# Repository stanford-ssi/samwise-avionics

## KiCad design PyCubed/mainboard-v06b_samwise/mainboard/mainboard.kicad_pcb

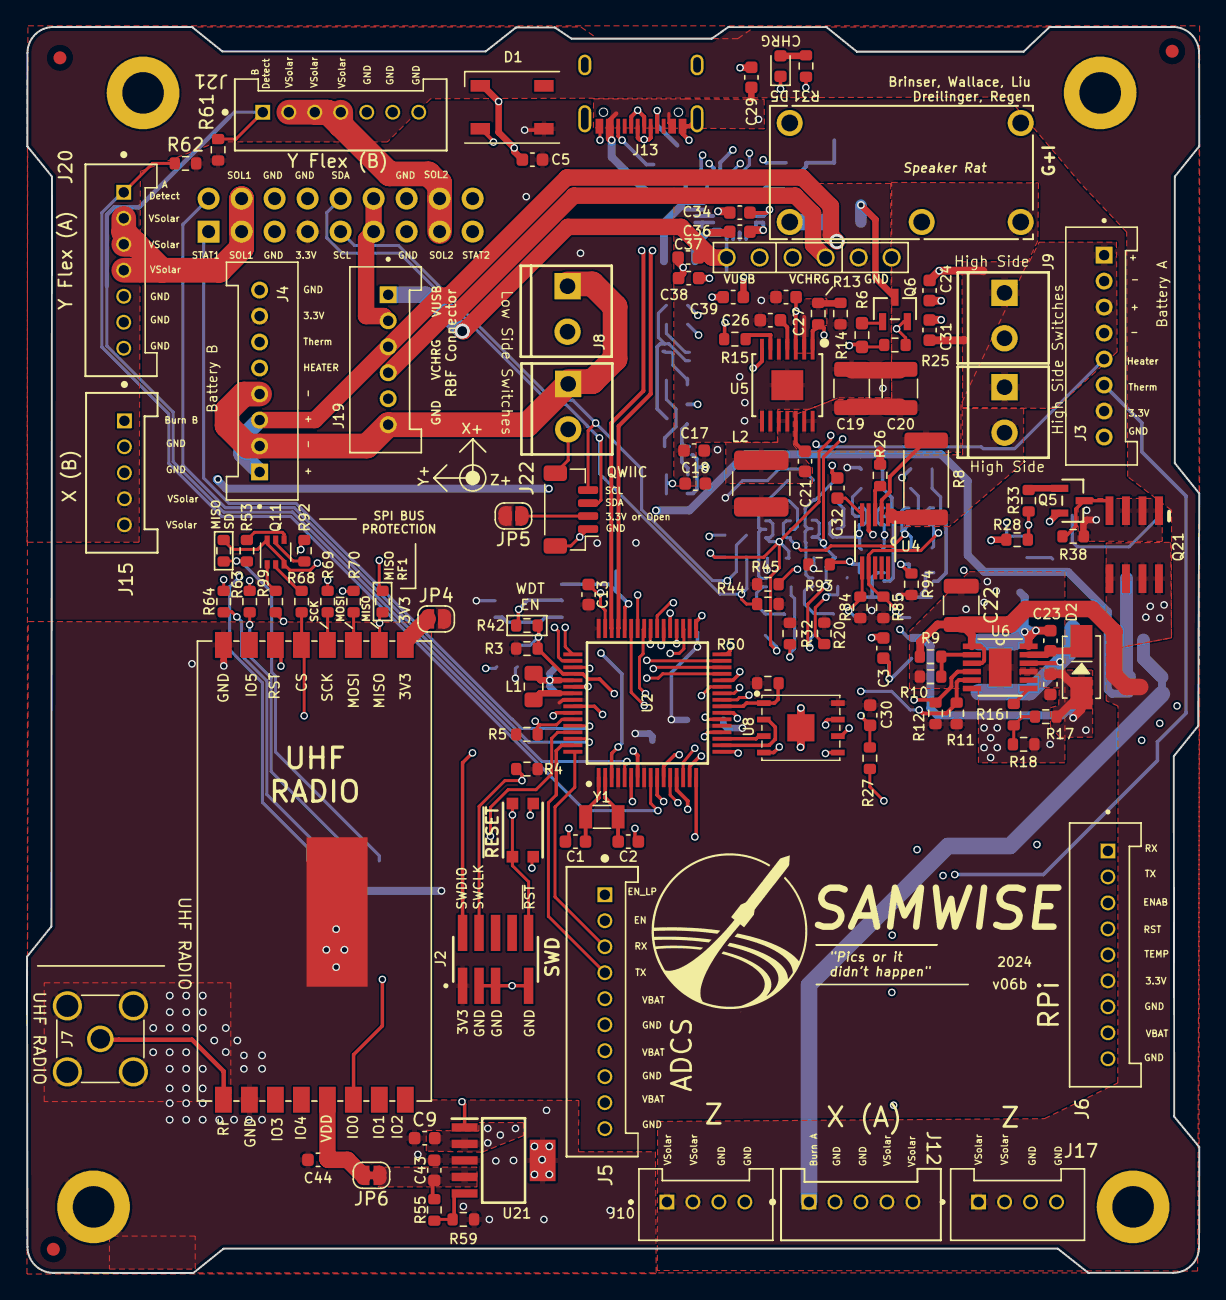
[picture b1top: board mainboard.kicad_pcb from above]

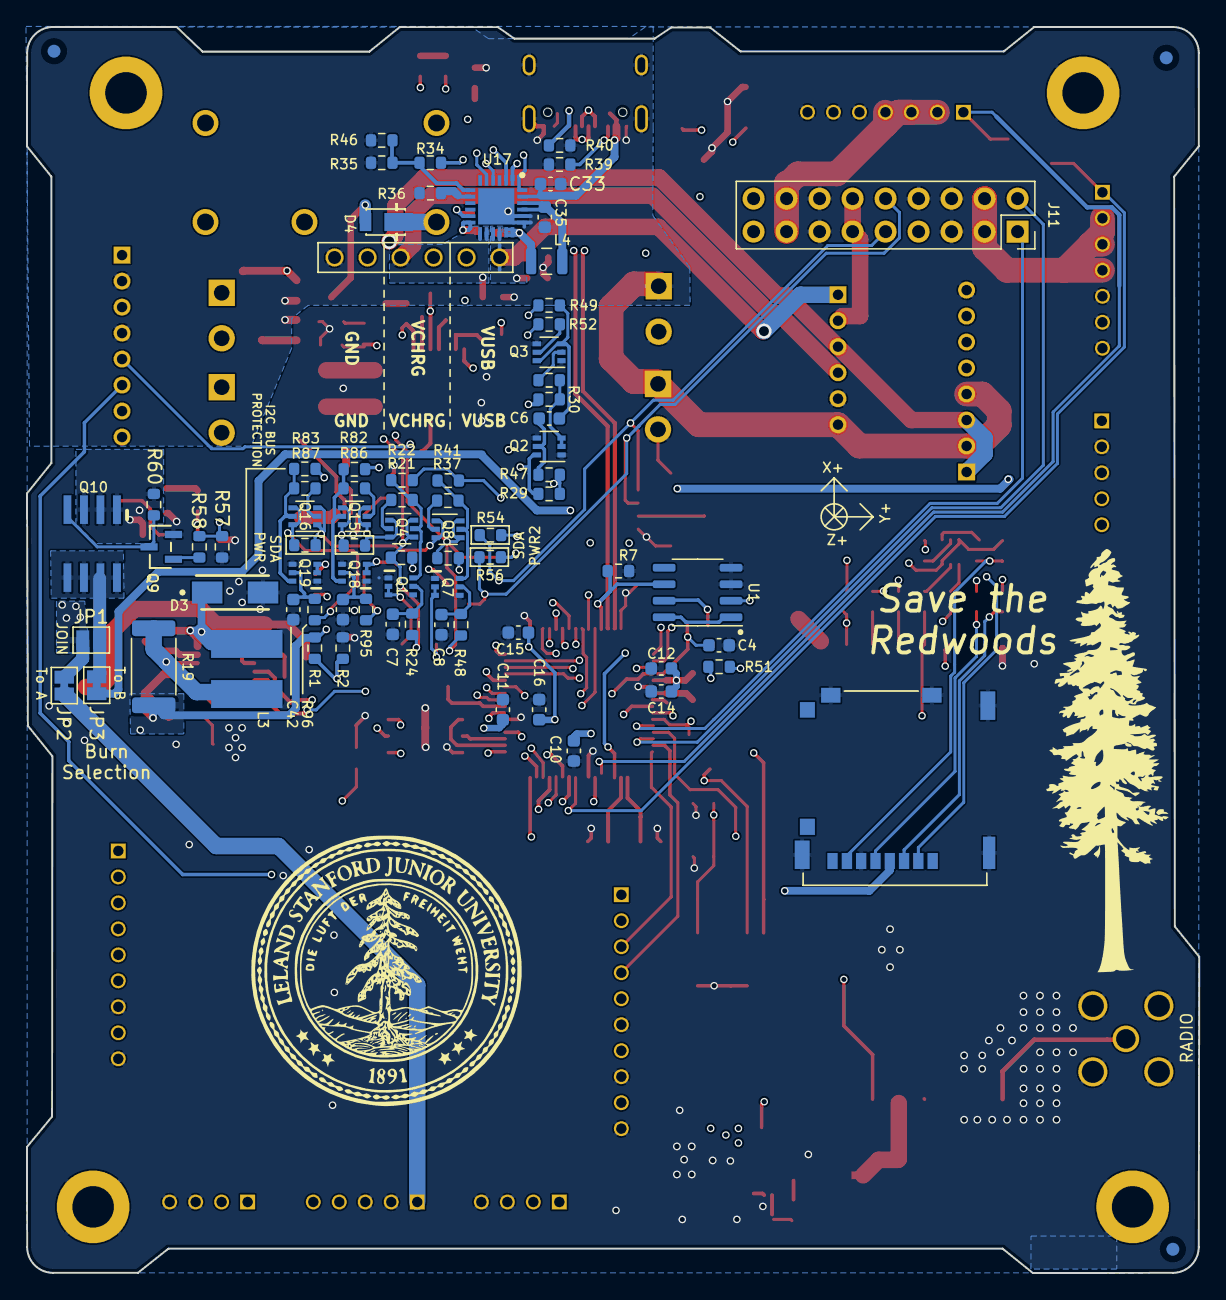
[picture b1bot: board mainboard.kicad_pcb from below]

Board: 4 copper layers, 90.2 x 95.9 mm, 201 parts (79 on the bottom side), 144 nets.

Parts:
C1, C2: 8pF; C_0603_1608Metric
C3, C5, C10, C11, C21, C24, C30: 0.1uF; C_0603_1608Metric
C4, C12, C13, C15, C23, C27, C33: 1uF; C_0603_1608Metric
C6, C9, C14, C16, C25, C35, C39, C43, C44: 10uF; C_0603_1608Metric
C7, C8, C41, C42: 10nF; C_0603_1608Metric
C17, C18, C31, C37, C38: 22uF; C_0603_1608Metric
C19, C20, C22: 10uF; C_1210_3225Metric
C26, C32: 3.3nF; C_0603_1608Metric
C29, C34: 4.7uF; C_0603_1608Metric
C36: 47nF; C_0603_1608Metric
D1: SK6812; LED_WS2812B_PLCC4_5.0x5.0mm_P3.2mm
D2: CDBA240LL; DO-214AC
D3: CMSH1-40M; DIOM5226X262N
D4: DFLS130L; PWRDI-123
D5: GREEN LED; LED_0603_1608Metric
H1, H2, H3, H4: MountingHole_Pad; MountingHole_3.2mm_M3_DIN965_Pad
J1: 503182-1852; MOLEX_503182-1852
J2: Conn_ARM_JTAG_SWD_10; SAMTEC_FTSH-105-01-L-DV-007
J3, J4: 353620850
J5: 353621050; MOLEX_35362-1050
J6: 353620950; MOLEX_35362-0950
J7: Amphenol_901-144; SMA_901-144-horizontal
J8, J9, J16, J18: 1985807; SCREWTERMINAL-3.5MM-2_LOCK
J10, J17: 353620450; MOLEX_35362-0450
J11: MPPT board; PinSocket_2x09_P2.54mm_Vertical
J12, J15: 353620550; MOLEX_35362-0550
J13: USB_C_pycubed; USB_C_Receptacle_XKB_U262-161N-4BVC11
J14: Conn_01x06_Horizontal; PinHeader_1x06_P2.54mm_Vertical_J14
J19: 353620650; MOLEX_35362-0650
J20, J21: 353620750; MOLEX_35362-0750
J22: QWIIC; JST_SH_BM04B-SRSS-TB_1x04-1MP_P1.00mm_Vertical
JP1: Jumper_2_Open; SolderJumper-2_P1.3mm_Open_Pad1.0x1.5mm
JP2, JP3: Jumper_2_Bridged; SolderJumper-2_P1.3mm_Bridged_Pad1.0x1.5mm
JP4: 3.3V EN; SolderJumper-2_P1.3mm_Open_RoundedPad1.0x1.5mm
JP5: QWIIC suply; SolderJumper-2_P1.3mm_Open_RoundedPad1.0x1.5mm
JP6: Jumper_3_Bridged12; SolderJumper-2_P1.3mm_Bridged_RoundedPad1.0x1.5mm
L1: 10uH; L_0805_2012Metric_Pad1.15x1.40mm_HandSolder
L2: 3.3uH; L_2141
L3: 68uH; SDE06004A-680K
L4: 1uH; L_2510
Q1, Q7, Q18, Q19: BSS138DWQ-7
Q2, Q3, Q4, Q8, Q15, Q16: MBT2222ADW1T1; SOT-363_SC-70-6
Q5, Q9: IRLML2803; SOT-23
Q6: BC817-40,215; SOT-23
Q10, Q21: DMP2040USS-13; IRF7404TRPBF
Q11: MMDT2907; SOT-363_SC-70-6
R1, R18: 330k; R_0603_1608Metric
R2: 110k; R_0603_1608Metric
R3, R4, R5, R7, R22, R23, R25, R28, R31, R41, R43, R44, R45, R46, R50, R51, R52, R55, R57, R82, R83, R84, R85: 10k; R_0603_1608Metric
R6: 2.1k; R_0603_1608Metric_Pad0.98x0.95mm_HandSolder
R8: 0.02; R_2512_6332Metric
R9: 121k; R_0603_1608Metric
R10, R14: 22.1k; R_0603_1608Metric
R11, R12, R15, R20, R27, R30, R32, R38, R49, R60, R61, R62, R93, R94: 100k; R_0603_1608Metric
R13, R29: 73.2k; R_0603_1608Metric
R16: 50k; R_0603_1608Metric
R17: 510k; R_0603_1608Metric
R19: 0.40; R_2512_6332Metric
R21, R37, R86, R87: 680; R_0603_1608Metric
R24, R47, R48, R95, R96: 200k; R_0603_1608Metric
R26, R63, R64, R69, R70: 1k; R_0603_1608Metric
R33, R58, R68, R92: 4.7k; R_0603_1608Metric
R34: 5.23k; R_0603_1608Metric
R35: 30.1k; R_0603_1608Metric
R36: 560; R_0603_1608Metric
R39, R40: 5.1k; R_0603_1608Metric
R42: 100; R_0603_1608Metric
R53, R54, R56, R99, R101, R104, R108, R109: 0; R_0603_1608Metric
R59: 3.3k; R_0603_1608Metric
R110: 20k; R_0603_1608Metric
REF1B, REF1T, REF2B, REF2T, REF3B, REF3T: Fiducial_1mm_Mask2mm
SW1: KMR231NG LFS; BTN_KMR2_4.6X2.8
U1: MAX706RESA; SO-8_3.9x4.9mm_P1.27mm
U2: ATSAMD51J20A-AU; QFP50P1200X1200X120-64N
U4: ADM1176-1ARMZ-R7
U5: TPS54226PWPR; PWP14_2P31X2P46-L
U6: LT3652HVIMSE#PBF; MSOP-12_MSE
U8: MR25H40MDF; SON127P600X500X90-9N
U16: PE014006; RELAY_PE014006
U17: BQ25883RGER; QFN50P400X400X100-25N-D
U21: TPS7A4501DCQT
U23: RFM98PW
Y1: 32.768kHz; Crystal_SMD_3215-2Pin_3.2x1.5mm

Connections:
3.3V: C5.1, C10.1, C11.1, C13.1, C15.1, C16.1, C17.2, C18.2, C30.1, D1.1 (VDD), J1.4 (VDD), J2.1 (VTref), J3.7, J4.7, J6.6, J11.7, JP4.2 (B), JP5.2 (B), L2.2, R3.1, R4.1, R5.1, R11.2, R12.2, R13.2, R20.1, R22.1, R23.1, R32.1, R41.1, R43.1, R44.1, R45.1, R50.2, R51.2, R61.1, R62.1, R82.1, R83.1, R84.1, R85.1, R93.1, R94.1, U1.2 (VCC), U2.4 (PA03), U2.8 (VDDANA), U2.21 (VDDIO), U2.34 (VDDIO1), U2.48 (VDDIO2), U2.56 (VDDIO3), U5.1 (VO), U8.8 (VDD)
/Avionics/BATTERY: C3.1, R1.2, R2.2, U2.15 (PA06)
/Avionics/XTAL1: C1.1, U2.1 (PA00), Y1.1
/Avionics/XTAL2: C2.1, U2.2 (PA01), Y1.2
/Burn Wires/BURN_AOUT: JP1.1 (A), JP2.1 (A), Q21.5 (Drain), Q21.6 (Drain), Q21.7 (Drain), Q21.8 (Drain)
/Burn Wires/BURN_BOUT: JP1.2 (B), JP3.1 (A), Q10.5 (Drain), Q10.6 (Drain), Q10.7 (Drain), Q10.8 (Drain)
/Burn Wires/VBURN_A_IN: Q10.1 (Source), Q10.2 (Source), Q10.3 (Source), Q21.1 (Source), Q21.2 (Source), Q21.3 (Source), R38.2, R60.2, U16.11
/Connectors/VSOLAR_DEPL1: J11.3, J11.4, J20.2, J20.3, J20.4
/Connectors/VSOLAR_DEPL2: J11.15, J11.16, J21.2, J21.3, J21.4
/Power/3V3_EN: Q2.6 (C1), R29.2, U5.7 (EN)
/Power/REGN: C34.1, R31.2, U17.11 (REGN)
/Power/V_RF: C43.2, JP6.1 (A), R55.1, U21.4 (OUT)
/RF/RF1_ANT: J7.1 (In), U23.1 (ANT)
ADCS_EN: J5.2, U2.43 (PA22)
ADCS_EN_LP: J5.1, U2.41 (PA20)
ADCS_Rx: J5.3, U2.64 (PB03)
ADCS_Tx: J5.4, U2.63 (PB02)
BAT_HEATER_A: J3.5, U2.39 (PB16)
BAT_HEATER_B: J4.5, U2.40 (PB17)
BURN_A: J12.1, JP2.2 (B)
BURN_B: J15.1, JP3.2 (B)
BURN_RELAY_A: R6.1, R25.1, U2.28 (PB15)
ENAB_BURN_A: R28.1, R33.2, U2.32 (PA15)
ENAB_BURN_B: R57.1, R58.2, U2.14 (PA05)
ENAB_RF: U2.6 (PB05), U21.1 (~SHDN)
FLASH_CS: R50.1, U2.24 (PB11), U8.1 (~CS)
FLASH_IO2: U2.19 (PA10), U8.3 (~WP)
FLASH_IO3: U2.20 (PA11), U8.7 (~HOLD)
FLASH_MISO: U2.18 (PA09), U8.2 (SO)
FLASH_MOSI: U2.17 (PA08), U8.5 (SI)
FLASH_SCK: U2.23 (PB10), U8.6 (SCK)
GND: C1.2, C2.2, C3.2, C4.1, C5.2, C7.2, C8.2, C9.1, C10.2, C11.2, C12.1, C13.2, C14.2, C15.2, C16.2, C17.1, C18.1, C19.2, C20.2, C22.1, C25.1, C26.2, C27.2, C30.2, C32.1, C41.2, C42.2, C43.1, C44.1, D1.3 (VSS), D3.2 (A), H1.1, H2.1, H3.1, H4.1, J1.6 (VSS), J1.P1 (SHIELD), J1.P2 (SHIELD), J1.P3 (SHIELD), J1.P4 (SHIELD), J1.P5 (SHIELD), J2.3 (GND), J2.5 (GND), J2.9 (GNDDetect), J3.8, J4.8, J5.6, J5.8, J5.10, J6.7, J6.9, J7.2 (Ext), J8.2, J10.3, J10.4, J11.5, J11.6, J11.8, J11.13, J11.14, J12.2, J12.3, J14.5, J15.2, J15.3, J17.3, J17.4, J18.2, J19.5, J20.5, J20.6, J20.7, J21.5, J21.6, J21.7, J22.1, J22.MP (MountPin), Q1.1 (S2), Q1.4 (S1), Q2.1 (E1), Q2.4 (E2), Q3.1 (E1), Q3.4 (E2), Q5.2 (S), Q6.2 (E), Q7.1 (S2), Q7.4 (S1), Q9.2 (S), Q18.1 (S2), Q18.4 (S1), Q19.1 (S2), Q19.4 (S1), R2.1, R7.1, R10.2, R14.1, R18.2, R25.2, R27.1, R28.2, R57.2, R59.2, SW1.B (S), SW1.B' (S1), U1.3 (GND), U1.4 (PFI), U2.7 (GND), U2.22 (GND1), U2.33 (GND2), U2.47 (GND3), U2.54 (GND4), U4.4 (GND), U5.5 (GND), U5.8 (PGND1), U5.9 (PGND2), U5.15 (EPAD), U6.6 (TIMER), U6.13 (EPAD), U8.4 (VSS), U8.9 (EP), U16.12, U21.3 (GND_1), U21.6 (GND_2), U23.2 (GND), U23.16 (GND), U23.17 (GND)
GNDREF: C24.2, C29.2, C31.2, C33.1, C34.2, C35.1, C37.1, C38.1, C39.1, J3.2, J3.4, J4.2, J4.4, J8.1, J13.A1 (GND), J13.A12 (GND), J13.S1 (SHIELD), J14.6, J18.1, J19.6, R35.1, R36.1, R39.1, R40.1, R46.1, U17.19 (GND_1), U17.20 (GND_2), U17.25 (EP)
MISO: Q11.3 (C2), Q11.6 (C1), R101.2, R104.2, U2.31 (PA14)
MISO_RF1: R99.2, R101.1, U23.10 (MISO)
MISO_SD: J1.7 (DAT0), R53.2, R104.1
MOSI: R64.2, R70.1, U2.29 (PA12)
MOSI_RF1: R70.2, U23.11 (MOSI)
MOSI_SD: J1.3 (CMD), R64.1
MPPT_STAT_1: J11.1, U2.60 (PB31)
MPPT_STAT_2: J11.17, U2.49 (PB22)
unnamed: D1.4 (DIN), U2.42 (PA21)
unnamed: C23.1, D2.1 (K), U6.11 (BOOST)
unnamed: C23.2, D3.1 (K), L3.1, U6.12 (SW)
unnamed: D5.2 (A), R31.1
unnamed: C37.2, C38.2, J14.1, J19.1, U17.15 (SYS_1), U17.16 (SYS_2)
unnamed: C39.2, J14.4, J19.4, U17.13 (BAT_1), U17.14 (BAT_2)
unnamed: J22.2, JP5.1 (A)
unnamed: JP4.1 (A), U23.9 (3.3V)
unnamed: Q1.6 (D1), Q4.5 (B2), R21.2, R22.2
unnamed: Q1.2 (G2), Q1.3 (D2), R20.2
unnamed: C7.1, Q1.5 (G1), R24.2
unnamed: Q2.2 (B1), Q2.3 (C2), R30.2, R110.2
unnamed: C6.2, Q2.5 (B2), R47.2
unnamed: Q3.2 (B1), R110.1
unnamed: C6.1, Q3.3 (C2), Q3.6 (C1), R49.2
unnamed: Q3.5 (B2), R52.1
unnamed: Q4.2 (B1), R21.1
unnamed: Q5.1 (G), R33.1
unnamed: Q6.1 (B), R6.2
unnamed: D4.A, Q6.3 (C), U16.5 (A2)
unnamed: Q7.6 (D1), Q8.5 (B2), R37.2, R41.2
unnamed: Q7.2 (G2), Q7.3 (D2), R32.2
unnamed: C8.1, Q7.5 (G1), R48.2
unnamed: Q8.2 (B1), R37.1
unnamed: Q9.1 (G), R58.1
unnamed: Q9.3 (D), Q10.4 (Gate), R60.1
unnamed: Q11.2 (B1), R68.1
unnamed: Q11.1 (E1), R99.1
unnamed: Q11.5 (B2), R92.1
unnamed: Q11.4 (E2), R53.1
unnamed: Q15.2 (B1), R86.1
unnamed: Q15.5 (B2), Q18.6 (D1), R82.2, R86.2
unnamed: Q16.2 (B1), R87.1
unnamed: Q16.5 (B2), Q19.6 (D1), R83.2, R87.2
unnamed: Q18.2 (G2), Q18.3 (D2), R93.2
unnamed: C41.1, Q18.5 (G1), R95.2
unnamed: Q19.2 (G2), Q19.3 (D2), R94.2
unnamed: C42.1, Q19.5 (G1), R96.2
unnamed: Q5.3 (D), Q21.4 (Gate), R38.1
unnamed: R16.2, R17.2, R18.1
unnamed: U1.1 (~MR), U1.8 (~WDO)
unnamed: R42.2, U1.7 (~RESET)
unnamed: C12.2, C14.1, L1.1, U2.53 (VDDCORE)
unnamed: L1.2, U2.55 (VSW)
unnamed: R26.2, U4.3 (ON)
unnamed: C32.2, U4.5 (TIMER)
unnamed: R15.1, U5.6 (PG)
unnamed: C26.1, U5.4 (SS)
unnamed: C21.1, L2.1, U5.10 (SW1), U5.11 (SW2)
unnamed: C21.2, U5.12 (VBST)
unnamed: R13.1, R14.2, U5.2 (VFB)
unnamed: C27.1, R15.2, U5.3 (VREG5)
unnamed: L3.2, R19.1, U6.10 (SENSE)
unnamed: R16.1, U6.7 (VFB)
unnamed: R9.2, R10.1, U6.2 (VIN_REG)
unnamed: C36.2, U17.12 (BTST)
unnamed: R36.2, U17.8 (ILIM)
unnamed: C35.2, L4.1, U17.21 (PMID_1), U17.22 (PMID_2)
unnamed: C36.1, L4.2, U17.17 (SW_1), U17.18 (SW_2)
unnamed: R34.2, R35.2, R46.2, U17.7 (TS)
unnamed: R55.2, R59.1, U21.5 (SENSE/ADJ)
RF1_CS: R5.2, R68.2, U2.59 (PB30), U23.13 (NSS)
RF1_IO0: U2.61 (PB00), U23.6 (GPIO_0)
RF1_RST: U2.38 (PA19), U23.14 (RESET)
RPI_ENAB: J6.3, U2.10 (PB07)
RPI_RST: J6.4, R27.2, U2.12 (PB09)
RPI_TEMP: J6.5, U2.13 (PA04)
RPI_UART_FROM_PI: J6.1, U2.36 (PA17)
RPI_UART_TO_PI: J6.2, U2.35 (PA16)
SCK: R63.2, R69.2, U2.30 (PA13)
SCK_RF1: R69.1, U23.12 (SCK)
SCK_SD: J1.5 (CLK), R63.1
SCL: J11.9, J22.4, Q4.1 (E1), Q4.3 (C2), Q15.1 (E1), Q15.3 (C2), R45.2, R54.2, R108.2, U2.26 (PB13)
SCL_PWR: Q15.4 (E2), Q15.6 (C1), R84.2, R95.1, R108.1, U4.6 (SCL)
SCL_PWR2: Q4.4 (E2), Q4.6 (C1), R23.2, R24.1, R54.1, U17.5 (SCL)
SDA: J11.10, J22.3, Q8.1 (E1), Q8.3 (C2), Q16.1 (E1), Q16.3 (C2), R44.2, R56.2, R109.2, U2.25 (PB12)
SDA_PWR: Q16.4 (E2), Q16.6 (C1), R85.2, R96.1, R109.1, U4.7 (SDA)
SDA_PWR2: Q8.4 (E2), Q8.6 (C1), R43.2, R48.1, R56.1, U17.4 (SDA)
SD_CS: J1.2 (CD/DAT3), R51.1, R92.2, U2.51 (PA27)
SENSE_THERM_A: J3.6, U2.16 (PA07)
SENSE_THERM_B: J4.6, U2.3 (PA02)
STAT: D5.1 (K), U17.2 (STAT)
SWCLK: J2.4 (SWDCLK/TCK), R4.2, U2.57 (PA30)
SWDIO: J2.2 (SWDIO/TMS), U2.58 (PA31)
SideDeplyDetectA: J20.1, R62.2, U2.9 (PB06)
SideDeplyDetectB: J21.1, R61.2, U2.5 (PB04)
USB_CC1: J13.A5 (CC1), R40.2
USB_CC2: J13.B5 (CC2), R39.2
USB_D+: J13.A6 (D+), J13.B6 (D+), U2.46 (PA25), U17.24 (D+)
USB_D-: J13.A7 (D-), J13.B7 (D-), U2.45 (PA24), U17.1 (D-)
VBATT: C9.2, C19.1, C20.1, C25.2, D2.2 (A), D4.C, J5.5, J5.7, J5.9, J6.8, J11.11, J11.12, J14.2, J19.2, R1.1, R8.1, R17.1, R19.2, R26.1, R29.1, R30.1, R47.1, R49.1, U4.2 (SENSE), U5.13 (VIN), U5.14 (VCC), U6.9 (BAT), U16.1 (A1), U16.14, U21.2 (IN)
VBATT_SENSE: J9.2, J16.2, R8.2, U4.1 (VCC)
VBUS_IN: C29.1, C33.2, J13.A4 (VBUS), J13.A9 (VBUS), R34.1, U17.23 (VBUS)
VBUS_RESET: R52.2, U2.37 (PA18)
VCC_RF1: C44.2, JP6.2 (B), U23.5 (VCC)
VCHRG: C24.1, C31.1, J3.1, J3.3, J4.1, J4.3, J9.1, J14.3, J16.1, J19.3
VSOLAR: C22.2, J10.1, J10.2, J12.4, J12.5, J15.4, J15.5, J17.1, J17.2, R9.1, U6.1 (VIN), U6.3 (*SHDN)
WDT_WDI: R7.2, U1.6 (~WDI), U2.44 (PA23)
~FIXED_SOLAR_CHRG: R12.1, U2.11 (PB08), U6.4 (*CHRG)
~FIXED_SOLAR_FAULT: R11.1, U2.27 (PB14), U6.5 (*FAULT)
~MPPT_SHDN_1: J11.2, U2.62 (PB01)
~MPPT_SHDN_2: J11.18, U2.50 (PB23)
~RESET: C4.2, J2.10 (~RESET), R3.2, R42.1, SW1.A, SW1.A' (P1), U2.52 (RESETN)

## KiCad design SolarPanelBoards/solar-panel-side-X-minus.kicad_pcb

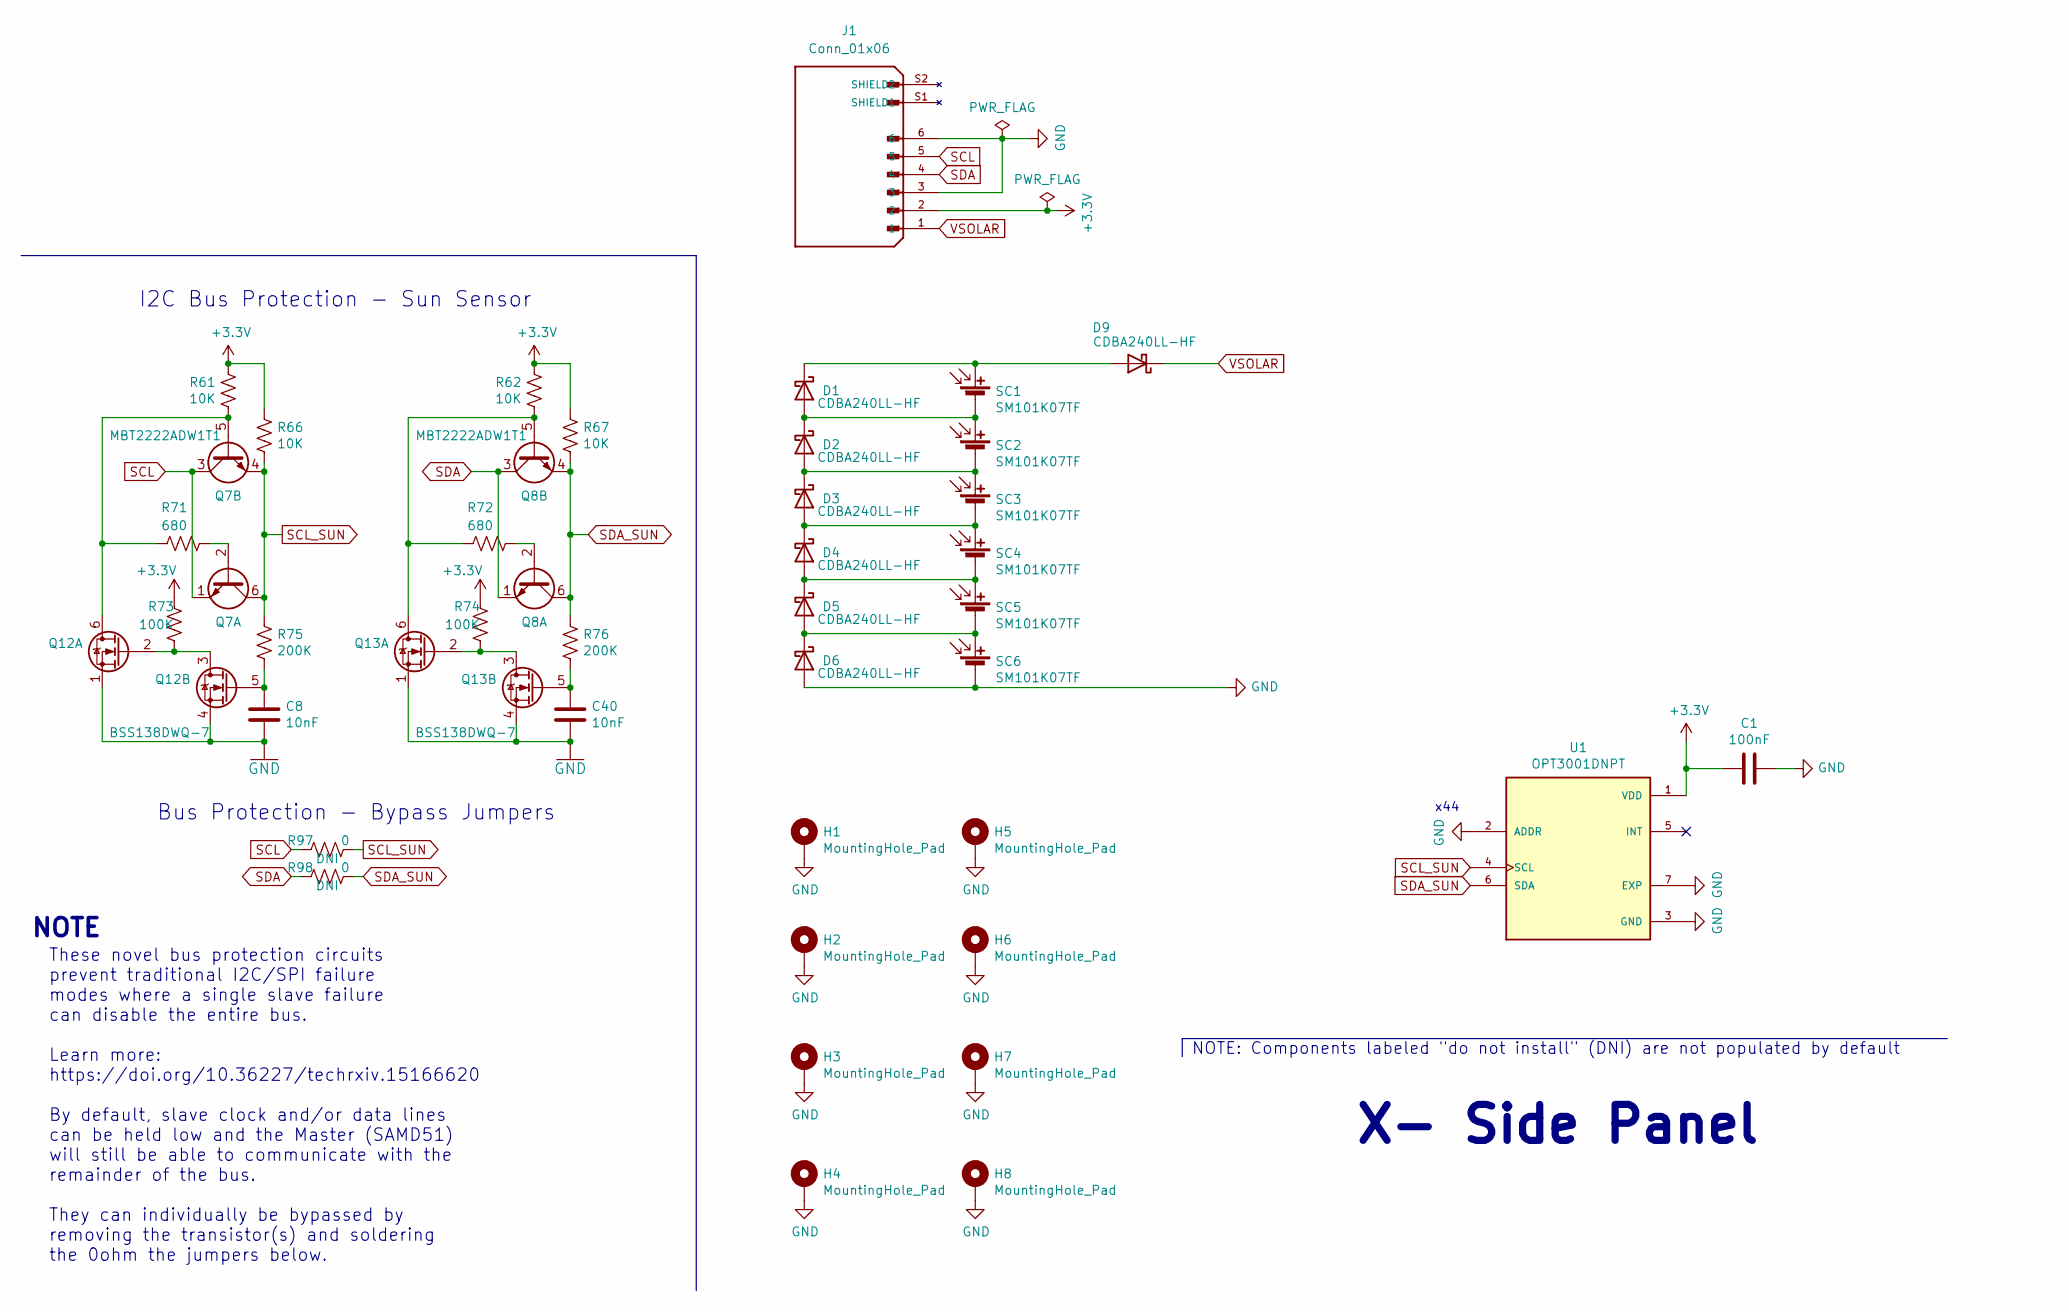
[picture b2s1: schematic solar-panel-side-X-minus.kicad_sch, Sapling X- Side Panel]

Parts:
C1: 100nF; C_0603_1608Metric
C8, C40: 10nF; C_0603_1608Metric
D1, D2, D3, D4, D5, D6, D9: CDBA240LL-HF; DO-214AC
H1, H2, H3, H4, H5, H6, H7, H8: MountingHole_Pad; MountingHole_2.2mm_M2_DIN965_Pad_TopBottom
J1: Conn_01x06; MOLEX_2053380006
Q7, Q8: MBT2222ADW1T1; SOT-363_SC-70-6; Manufacturer_Part_Number MBT2222ADW1T1G
Q12, Q13: BSS138DWQ-7; Manufacturer_Part_Number BSS138DWQ-7; Mouser Part Number 621-BSS138DWQ-7
R61, R62, R66, R67: 10K; R_0603_1608Metric
R71, R72: 680; R_0603_1608Metric
R73, R74: 100K; R_0603_1608Metric
R75, R76: 200K; R_0603_1608Metric
R97, R98: 0; R_0603_1608Metric
SC1, SC2, SC3, SC4, SC5, SC6: SM101K07TF
U1: OPT3001DNPT; OPT3001

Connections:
+3V3: C1.1, J1.2, R61.1, R62.1, R66.1, R67.1, R73.1, R74.1, U1.1 (VDD)
GND: C1.2, C8.2, C40.2, D6.2 (A), H1.1, H2.1, H3.1, H4.1, H5.1, H6.1, H7.1, H8.1, J1.3, J1.6, Q12.1 (S2), Q12.4 (S1), Q13.1 (S2), Q13.4 (S1), SC6.2 (-), U1.2 (ADDR), U1.3 (GND), U1.7 (EXP)
unnamed: D1.2 (A), D2.1 (K), SC1.2 (-), SC2.1 (+)
unnamed: D1.1 (K), D9.2 (A), SC1.1 (+)
unnamed: D2.2 (A), D3.1 (K), SC2.2 (-), SC3.1 (+)
unnamed: D3.2 (A), D4.1 (K), SC3.2 (-), SC4.1 (+)
unnamed: D4.2 (A), D5.1 (K), SC4.2 (-), SC5.1 (+)
unnamed: D5.2 (A), D6.1 (K), SC5.2 (-), SC6.1 (+)
unnamed: Q7.2 (B1), R71.1
unnamed: Q8.2 (B1), R72.1
unnamed: Q7.5 (B2), Q12.6 (D1), R61.2, R71.2
unnamed: Q12.2 (G2), Q12.3 (D2), R73.2
unnamed: C8.1, Q12.5 (G1), R75.2
unnamed: Q8.5 (B2), Q13.6 (D1), R62.2, R72.2
unnamed: Q13.2 (G2), Q13.3 (D2), R74.2
unnamed: C40.1, Q13.5 (G1), R76.2
SCL: J1.5, Q7.1 (E1), Q7.3 (C2), R97.2
SCL_SUN: Q7.4 (E2), Q7.6 (C1), R66.2, R75.1, R97.1, U1.4 (SCL)
SDA: J1.4, Q8.1 (E1), Q8.3 (C2), R98.2
SDA_SUN: Q8.4 (E2), Q8.6 (C1), R67.2, R76.1, R98.1, U1.6 (SDA)
VSOLAR: D9.1 (K), J1.1

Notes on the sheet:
NOTE
x44
I2C Bus Protection - Sun Sensor
X- Side Panel
Bus Protection - Bypass Jumpers
These novel bus protection circuits prevent traditional I2C/SPI failure modes where a single slave failure can disable the entire bus. Learn more: https://doi.org/10.36227/techrxiv.15166620 By default, slave clock and/or data lines can be held low and the Master (SAMD51) will still be able to commu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
NOTE: Components labeled "do not install" (DNI) are not populated by default

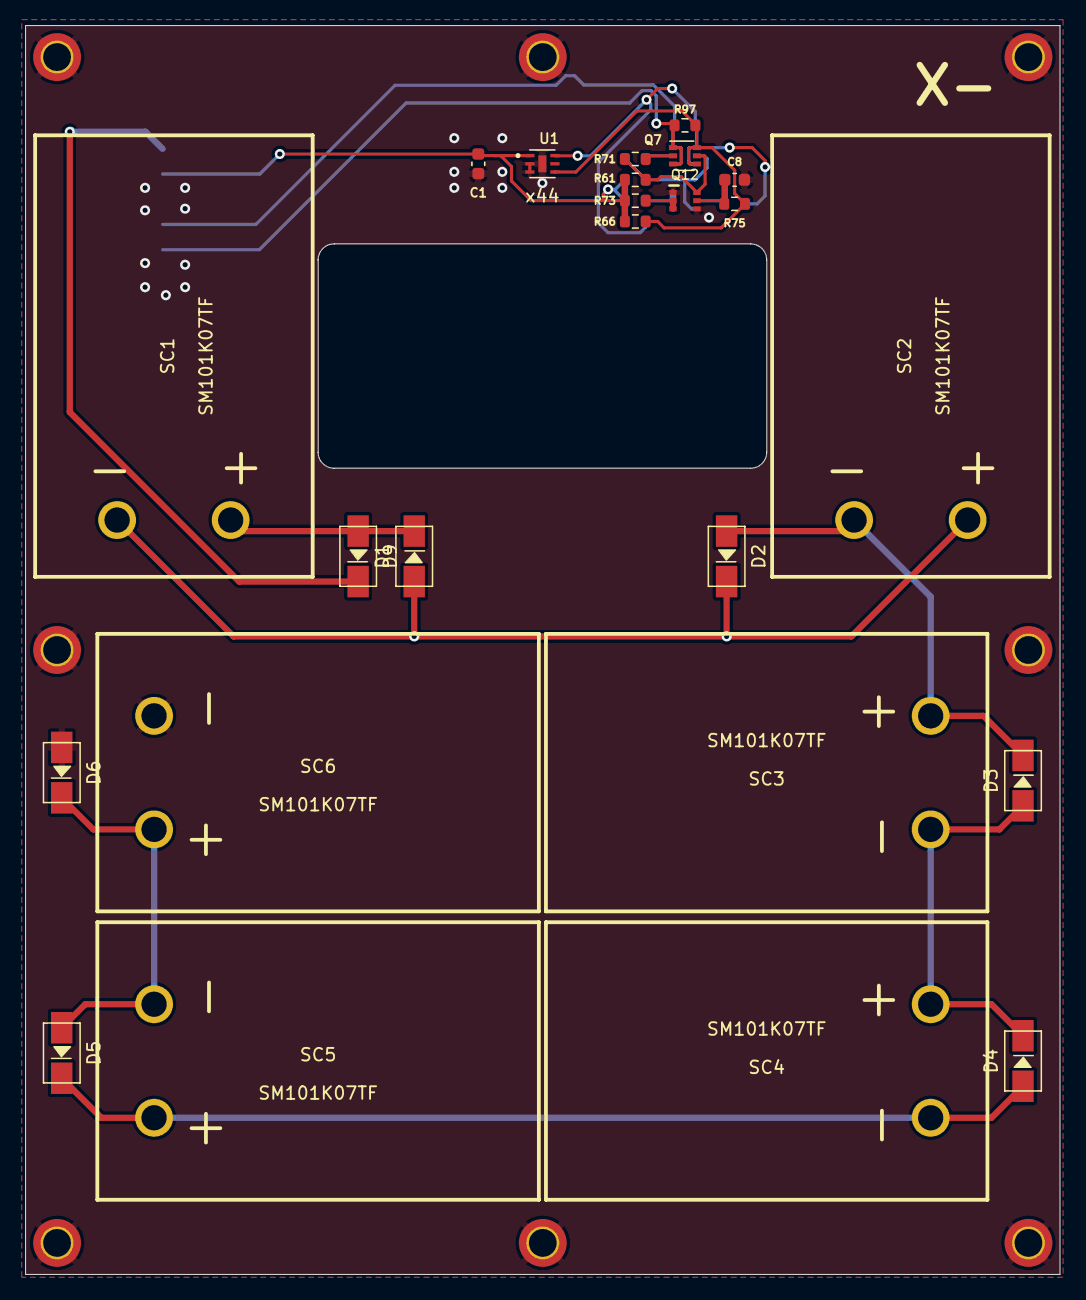
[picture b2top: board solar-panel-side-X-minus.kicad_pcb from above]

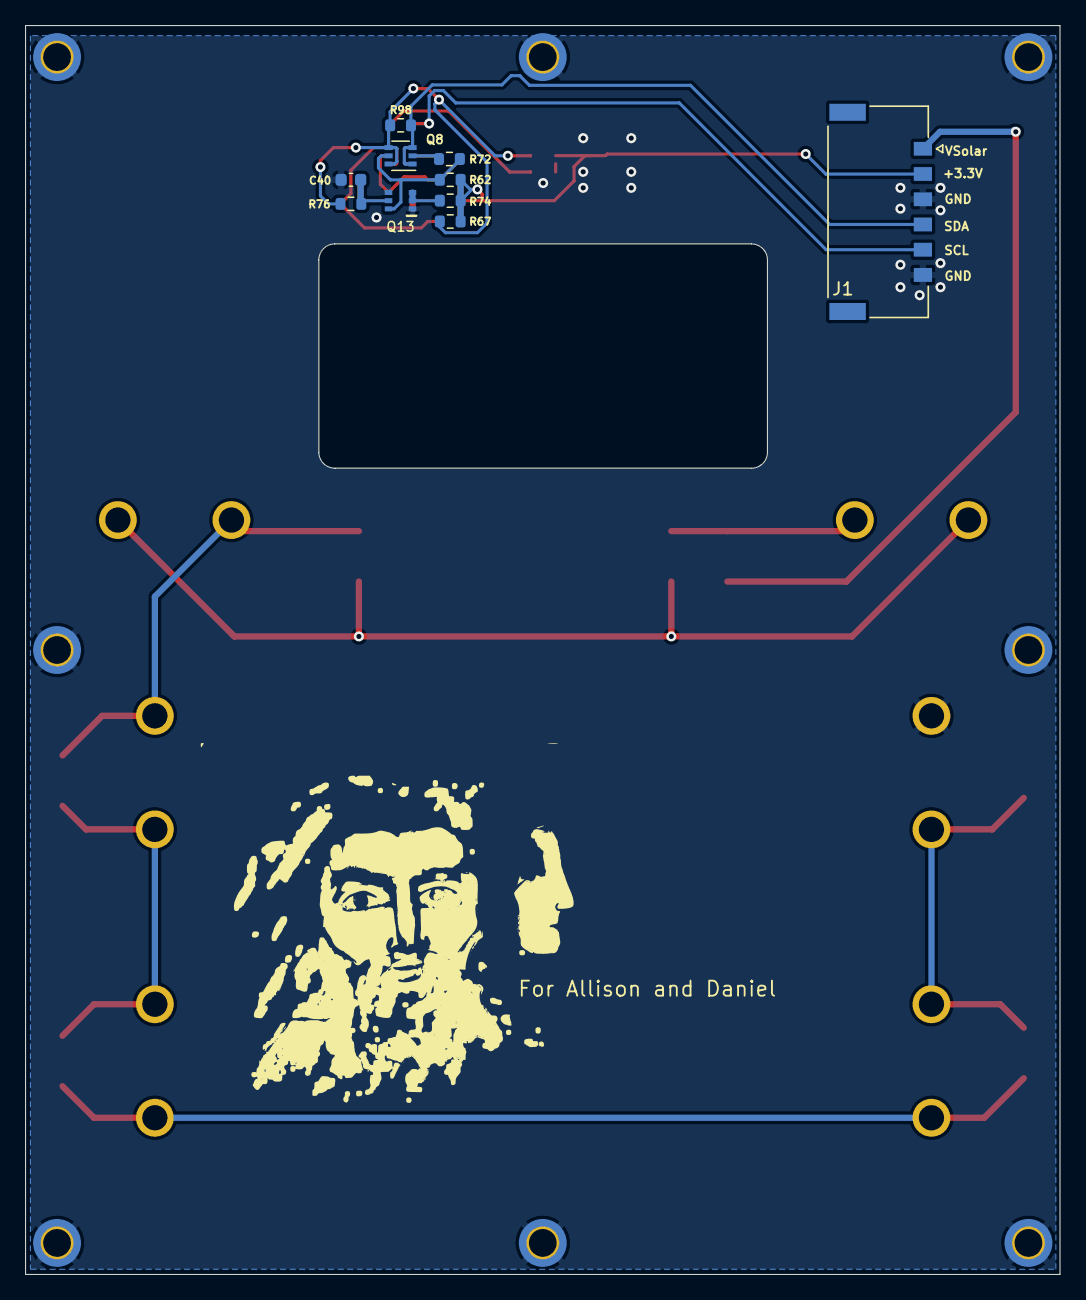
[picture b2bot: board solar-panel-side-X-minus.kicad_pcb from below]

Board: 2 copper layers, 82.0 x 99.0 mm, 42 parts (10 on the bottom side), 21 nets.

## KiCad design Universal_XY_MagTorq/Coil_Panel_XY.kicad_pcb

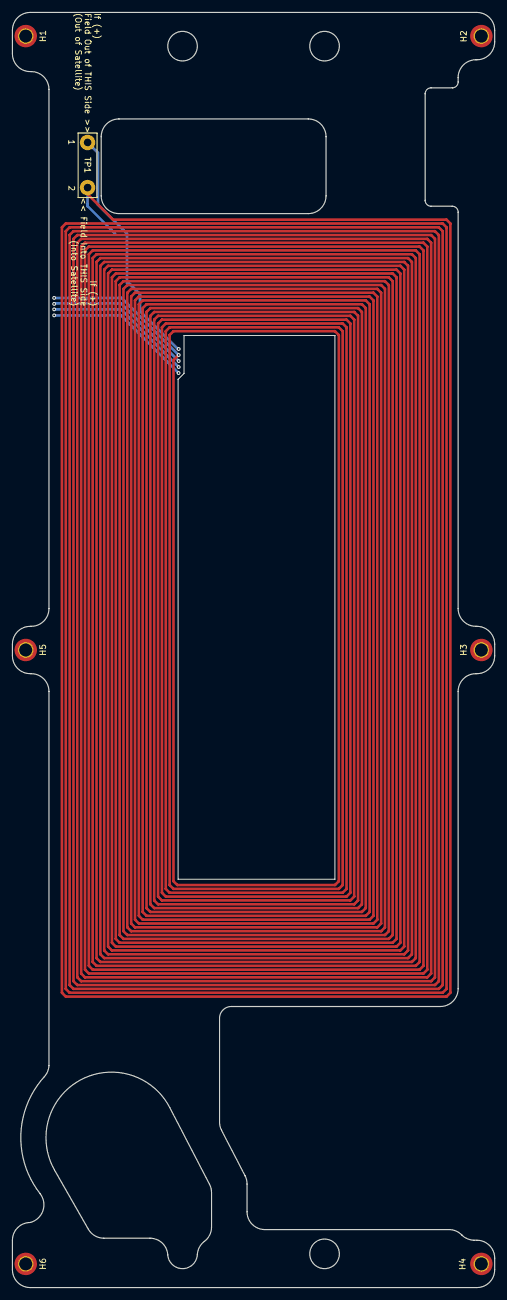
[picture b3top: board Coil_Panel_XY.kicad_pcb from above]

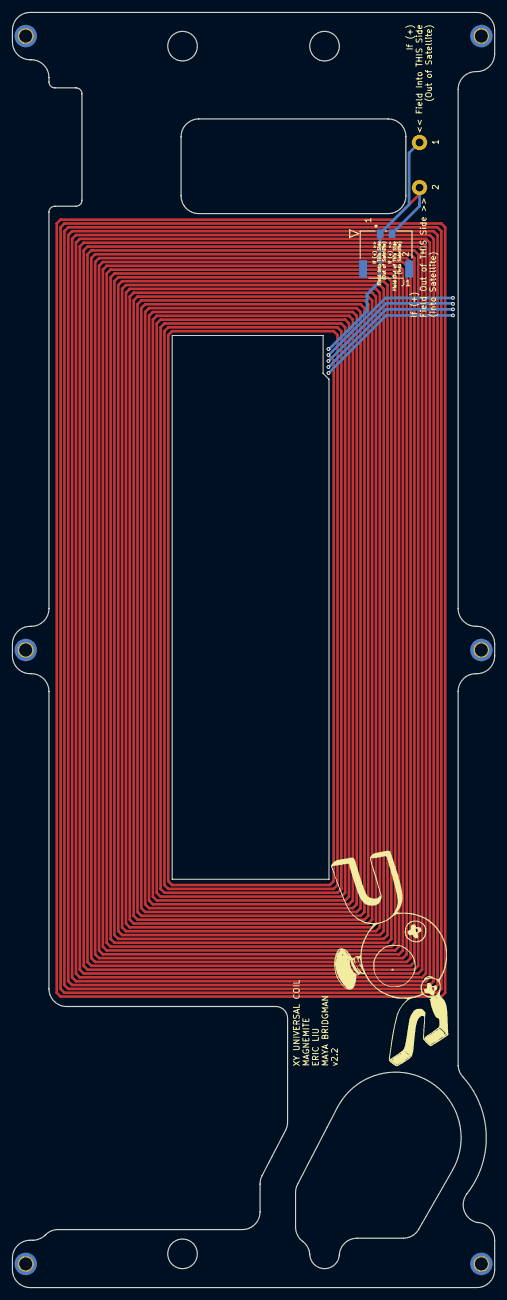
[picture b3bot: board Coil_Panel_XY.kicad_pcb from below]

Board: 6 copper layers, 81.5 x 215.5 mm, 9 parts (2 on the bottom side), 2 nets.

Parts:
H1, H2, H3, H4, H5, H6: MountingHole_Pad; MountingHole_2.2mm_M2_DIN965_Pad_TopBottom
J1: 205338-0002; Molex_205338-0002
NT1: NetTie_2; NetTie-2_SMD_Pad0.5mm
TP1: TestPointConnection

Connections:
COIL_1: J1.1, NT1.2, TP1.1
COIL_2: J1.2, NT1.1, TP1.2

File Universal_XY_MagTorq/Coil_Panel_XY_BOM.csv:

"Id";"Designator";"Footprint";"Quantity";"Designation";"Supplier and ref";
1;"TP1";"TestPointConnection";1;"Start/End of Coil Series";;;
2;"J1";"Molex_205338-0002";1;"2053380002";;;

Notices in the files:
parts and their libraries:
Copyright 2016 Accelerated Designs. All rights reserved.
Copyright 2021 Accelerated Designs. All rights reserved.
